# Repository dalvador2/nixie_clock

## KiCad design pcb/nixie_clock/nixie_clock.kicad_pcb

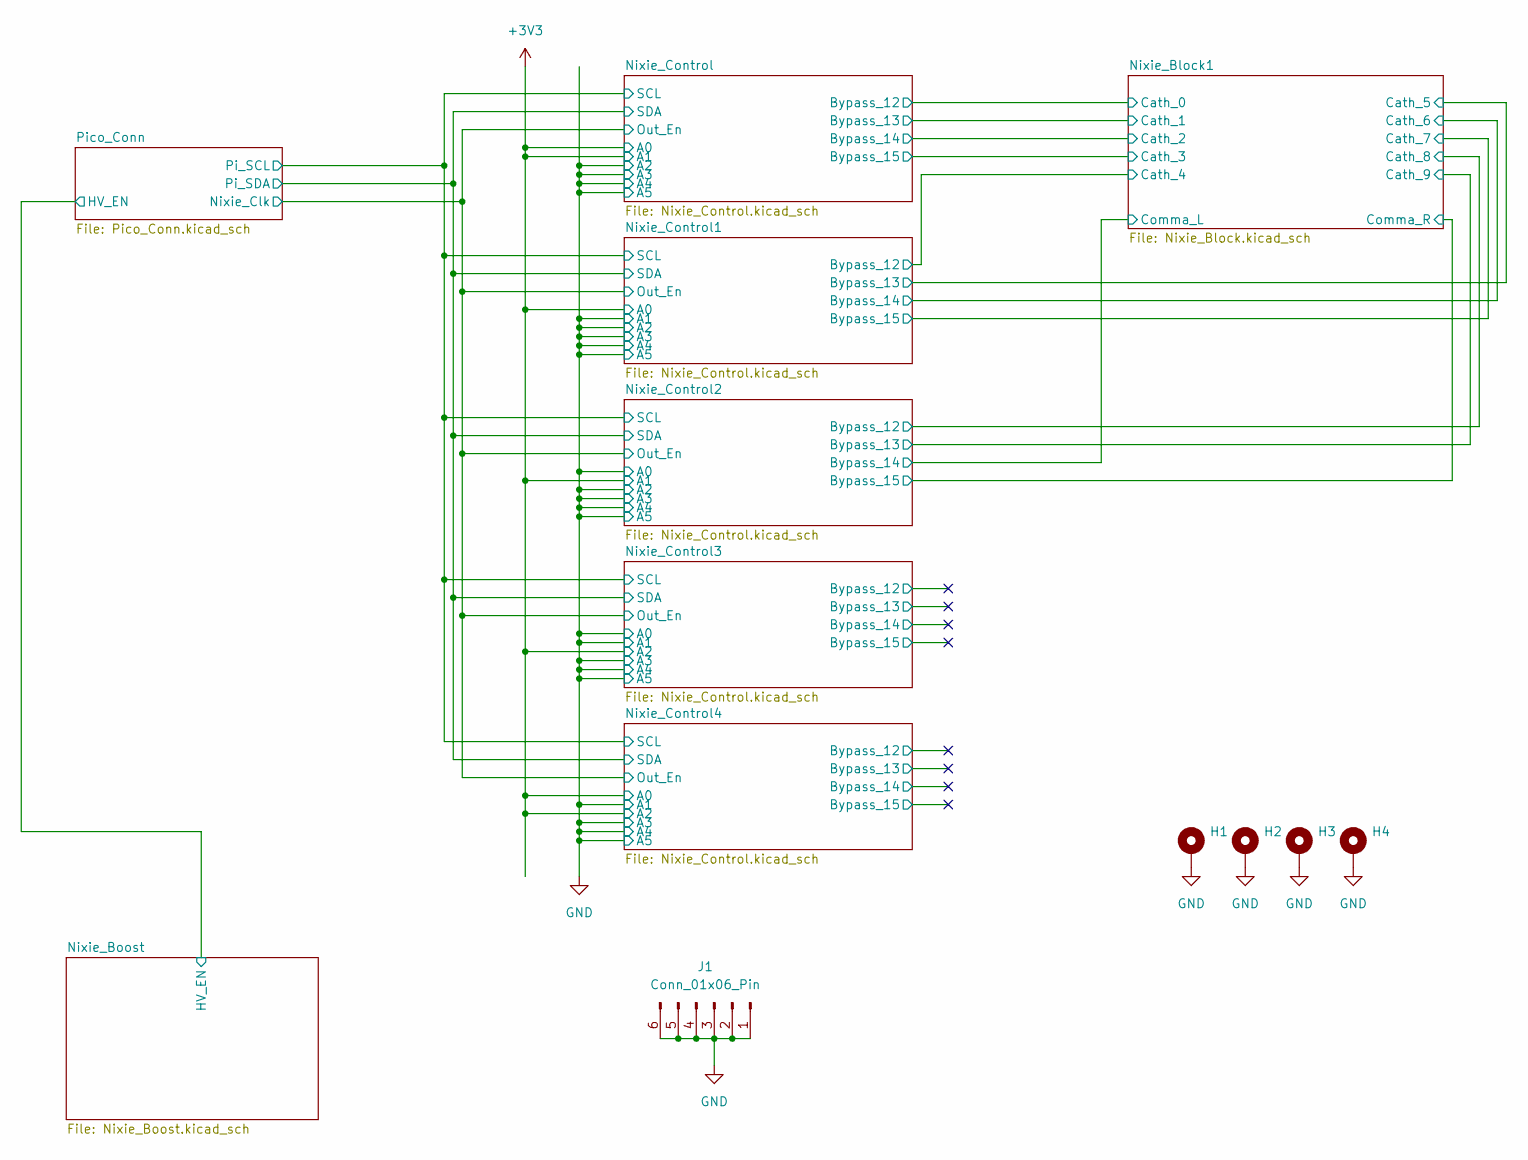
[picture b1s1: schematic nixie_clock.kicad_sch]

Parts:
H1, H2, H3, H4: MountingHole_Pad; MountingHole_2.7mm_M2.5_DIN965_Pad
J1: Conn_01x06_Pin; Molex_KK-254_AE-6410-06A_1x06_P2.54mm_Vertical

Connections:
GND: H1.1, H2.1, H3.1, H4.1, J1.1, J1.2, J1.3, J1.4, J1.5, J1.6; also elsewhere on the board

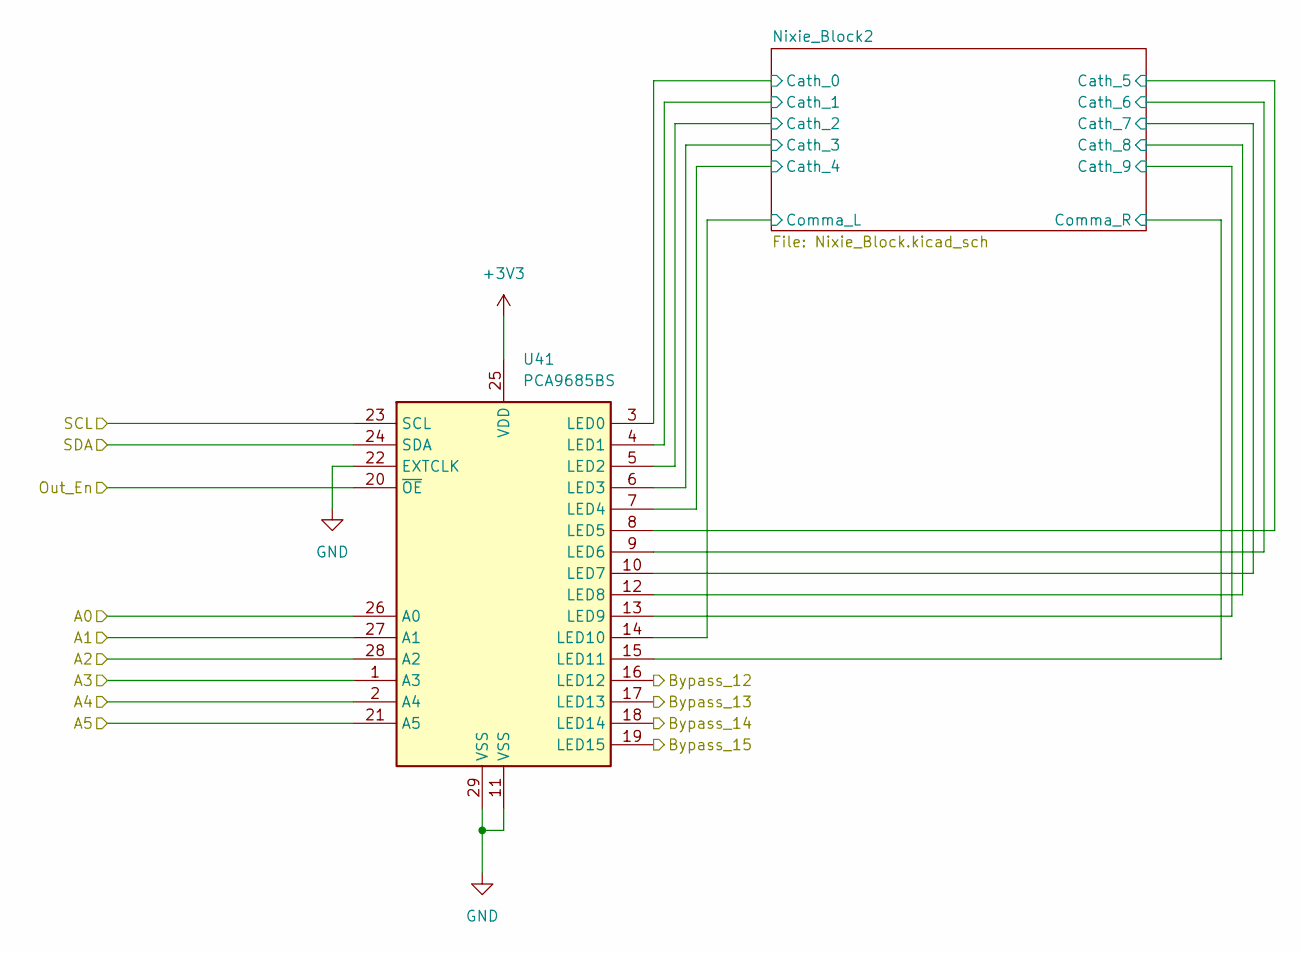
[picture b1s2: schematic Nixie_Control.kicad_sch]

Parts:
U41: PCA9685BS; QFN-28-1EP_6x6mm_P0.65mm_EP4.25x4.25mm; LCSC Part # C5191634

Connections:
+3V3: U41.25 (VDD), U41.28 (A2); also elsewhere on the board
/Nixie_Control3/Bypass_12: U41.16 (LED12)
/Nixie_Control3/Bypass_13: U41.17 (LED13)
/Nixie_Control3/Bypass_14: U41.18 (LED14)
/Nixie_Control3/Bypass_15: U41.19 (LED15)
/Nixie_Control3/Nixie_Block2/Cath_0: U41.3 (LED0); also elsewhere on the board
/Nixie_Control3/Nixie_Block2/Cath_1: U41.4 (LED1); also elsewhere on the board
/Nixie_Control3/Nixie_Block2/Cath_2: U41.5 (LED2); also elsewhere on the board
/Nixie_Control3/Nixie_Block2/Cath_3: U41.6 (LED3); also elsewhere on the board
/Nixie_Control3/Nixie_Block2/Cath_4: U41.7 (LED4); also elsewhere on the board
/Nixie_Control3/Nixie_Block2/Cath_5: U41.8 (LED5); also elsewhere on the board
/Nixie_Control3/Nixie_Block2/Cath_6: U41.9 (LED6); also elsewhere on the board
/Nixie_Control3/Nixie_Block2/Cath_7: U41.10 (LED7); also elsewhere on the board
/Nixie_Control3/Nixie_Block2/Cath_8: U41.12 (LED8); also elsewhere on the board
/Nixie_Control3/Nixie_Block2/Cath_9: U41.13 (LED9); also elsewhere on the board
/Nixie_Control3/Nixie_Block2/Comma_L: U41.14 (LED10); also elsewhere on the board
/Nixie_Control3/Nixie_Block2/Comma_R: U41.15 (LED11); also elsewhere on the board
/Nixie_Control/Out_En: U41.20 (~OE); also elsewhere on the board
/Nixie_Control/SCL: U41.23 (SCL); also elsewhere on the board
/Nixie_Control/SDA: U41.24 (SDA); also elsewhere on the board
GND: U41.1 (A3), U41.2 (A4), U41.11 (VSS), U41.21 (A5), U41.22 (EXTCLK), U41.26 (A0), U41.27 (A1), U41.29 (VSS); also elsewhere on the board

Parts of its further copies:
U13, U15, U28, U54: PCA9685BS; QFN-28-1EP_6x6mm_P0.65mm_EP4.25x4.25mm; LCSC Part # C5191634

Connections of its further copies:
+3V3: U13.25 (VDD), U13.26 (A0), U13.27 (A1), U15.25 (VDD), U15.26 (A0), U28.25 (VDD), U28.27 (A1), U54.25 (VDD), U54.26 (A0), U54.28 (A2); also elsewhere on the board
/Nixie_Block1/Cath_0: U13.16 (LED12); also elsewhere on the board
/Nixie_Block1/Cath_1: U13.17 (LED13); also elsewhere on the board
/Nixie_Block1/Cath_2: U13.18 (LED14); also elsewhere on the board
/Nixie_Block1/Cath_3: U13.19 (LED15); also elsewhere on the board
/Nixie_Block1/Cath_4: U15.16 (LED12); also elsewhere on the board
/Nixie_Block1/Cath_5: U15.17 (LED13); also elsewhere on the board
/Nixie_Block1/Cath_6: U15.18 (LED14); also elsewhere on the board
/Nixie_Block1/Cath_7: U15.19 (LED15); also elsewhere on the board
/Nixie_Block1/Cath_8: U28.16 (LED12); also elsewhere on the board
/Nixie_Block1/Cath_9: U28.17 (LED13); also elsewhere on the board
/Nixie_Block1/Comma_L: U28.18 (LED14); also elsewhere on the board
/Nixie_Block1/Comma_R: U28.19 (LED15); also elsewhere on the board
/Nixie_Control1/Nixie_Block2/Cath_0: U15.3 (LED0); also elsewhere on the board
/Nixie_Control1/Nixie_Block2/Cath_1: U15.4 (LED1); also elsewhere on the board
/Nixie_Control1/Nixie_Block2/Cath_2: U15.5 (LED2); also elsewhere on the board
/Nixie_Control1/Nixie_Block2/Cath_3: U15.6 (LED3); also elsewhere on the board
/Nixie_Control1/Nixie_Block2/Cath_4: U15.7 (LED4); also elsewhere on the board
/Nixie_Control1/Nixie_Block2/Cath_5: U15.8 (LED5); also elsewhere on the board
/Nixie_Control1/Nixie_Block2/Cath_6: U15.9 (LED6); also elsewhere on the board
/Nixie_Control1/Nixie_Block2/Cath_7: U15.10 (LED7); also elsewhere on the board
/Nixie_Control1/Nixie_Block2/Cath_8: U15.12 (LED8); also elsewhere on the board
/Nixie_Control1/Nixie_Block2/Cath_9: U15.13 (LED9); also elsewhere on the board
/Nixie_Control1/Nixie_Block2/Comma_L: U15.14 (LED10); also elsewhere on the board
/Nixie_Control1/Nixie_Block2/Comma_R: U15.15 (LED11); also elsewhere on the board
/Nixie_Control2/Nixie_Block2/Cath_0: U28.3 (LED0); also elsewhere on the board
/Nixie_Control2/Nixie_Block2/Cath_1: U28.4 (LED1); also elsewhere on the board
/Nixie_Control2/Nixie_Block2/Cath_2: U28.5 (LED2); also elsewhere on the board
/Nixie_Control2/Nixie_Block2/Cath_3: U28.6 (LED3); also elsewhere on the board
/Nixie_Control2/Nixie_Block2/Cath_4: U28.7 (LED4); also elsewhere on the board
/Nixie_Control2/Nixie_Block2/Cath_5: U28.8 (LED5); also elsewhere on the board
/Nixie_Control2/Nixie_Block2/Cath_6: U28.9 (LED6); also elsewhere on the board
/Nixie_Control2/Nixie_Block2/Cath_7: U28.10 (LED7); also elsewhere on the board
/Nixie_Control2/Nixie_Block2/Cath_8: U28.12 (LED8); also elsewhere on the board
/Nixie_Control2/Nixie_Block2/Cath_9: U28.13 (LED9); also elsewhere on the board
/Nixie_Control2/Nixie_Block2/Comma_L: U28.14 (LED10); also elsewhere on the board
/Nixie_Control2/Nixie_Block2/Comma_R: U28.15 (LED11); also elsewhere on the board
/Nixie_Control4/Bypass_12: U54.16 (LED12)
/Nixie_Control4/Bypass_13: U54.17 (LED13)
/Nixie_Control4/Bypass_14: U54.18 (LED14)
/Nixie_Control4/Bypass_15: U54.19 (LED15)
/Nixie_Control4/Nixie_Block2/Cath_0: U54.3 (LED0); also elsewhere on the board
/Nixie_Control4/Nixie_Block2/Cath_1: U54.4 (LED1); also elsewhere on the board
/Nixie_Control4/Nixie_Block2/Cath_2: U54.5 (LED2); also elsewhere on the board
/Nixie_Control4/Nixie_Block2/Cath_3: U54.6 (LED3); also elsewhere on the board
/Nixie_Control4/Nixie_Block2/Cath_4: U54.7 (LED4); also elsewhere on the board
/Nixie_Control4/Nixie_Block2/Cath_5: U54.8 (LED5); also elsewhere on the board
/Nixie_Control4/Nixie_Block2/Cath_6: U54.9 (LED6); also elsewhere on the board
/Nixie_Control4/Nixie_Block2/Cath_7: U54.10 (LED7); also elsewhere on the board
/Nixie_Control4/Nixie_Block2/Cath_8: U54.12 (LED8); also elsewhere on the board
/Nixie_Control4/Nixie_Block2/Cath_9: U54.13 (LED9); also elsewhere on the board
/Nixie_Control4/Nixie_Block2/Comma_L: U54.14 (LED10); also elsewhere on the board
/Nixie_Control4/Nixie_Block2/Comma_R: U54.15 (LED11); also elsewhere on the board
/Nixie_Control/Nixie_Block2/Cath_0: U13.3 (LED0); also elsewhere on the board
/Nixie_Control/Nixie_Block2/Cath_1: U13.4 (LED1); also elsewhere on the board
/Nixie_Control/Nixie_Block2/Cath_2: U13.5 (LED2); also elsewhere on the board
/Nixie_Control/Nixie_Block2/Cath_3: U13.6 (LED3); also elsewhere on the board
/Nixie_Control/Nixie_Block2/Cath_4: U13.7 (LED4); also elsewhere on the board
/Nixie_Control/Nixie_Block2/Cath_5: U13.8 (LED5); also elsewhere on the board
/Nixie_Control/Nixie_Block2/Cath_6: U13.9 (LED6); also elsewhere on the board
/Nixie_Control/Nixie_Block2/Cath_7: U13.10 (LED7); also elsewhere on the board
/Nixie_Control/Nixie_Block2/Cath_8: U13.12 (LED8); also elsewhere on the board
/Nixie_Control/Nixie_Block2/Cath_9: U13.13 (LED9); also elsewhere on the board
/Nixie_Control/Nixie_Block2/Comma_L: U13.14 (LED10); also elsewhere on the board
/Nixie_Control/Nixie_Block2/Comma_R: U13.15 (LED11); also elsewhere on the board
/Nixie_Control/Out_En: U13.20 (~OE), U15.20 (~OE), U28.20 (~OE), U54.20 (~OE); also elsewhere on the board
/Nixie_Control/SCL: U13.23 (SCL), U15.23 (SCL), U28.23 (SCL), U54.23 (SCL); also elsewhere on the board
/Nixie_Control/SDA: U13.24 (SDA), U15.24 (SDA), U28.24 (SDA), U54.24 (SDA); also elsewhere on the board
GND: U13.1 (A3), U13.2 (A4), U13.11 (VSS), U13.21 (A5), U13.22 (EXTCLK), U13.28 (A2), U13.29 (VSS), U15.1 (A3), U15.2 (A4), U15.11 (VSS), U15.21 (A5), U15.22 (EXTCLK), U15.27 (A1), U15.28 (A2), U15.29 (VSS), U28.1 (A3), U28.2 (A4), U28.11 (VSS), U28.21 (A5), U28.22 (EXTCLK), U28.26 (A0), U28.28 (A2), U28.29 (VSS), U54.1 (A3), U54.2 (A4), U54.11 (VSS), U54.21 (A5), U54.22 (EXTCLK), U54.27 (A1), U54.29 (VSS); also elsewhere on the board

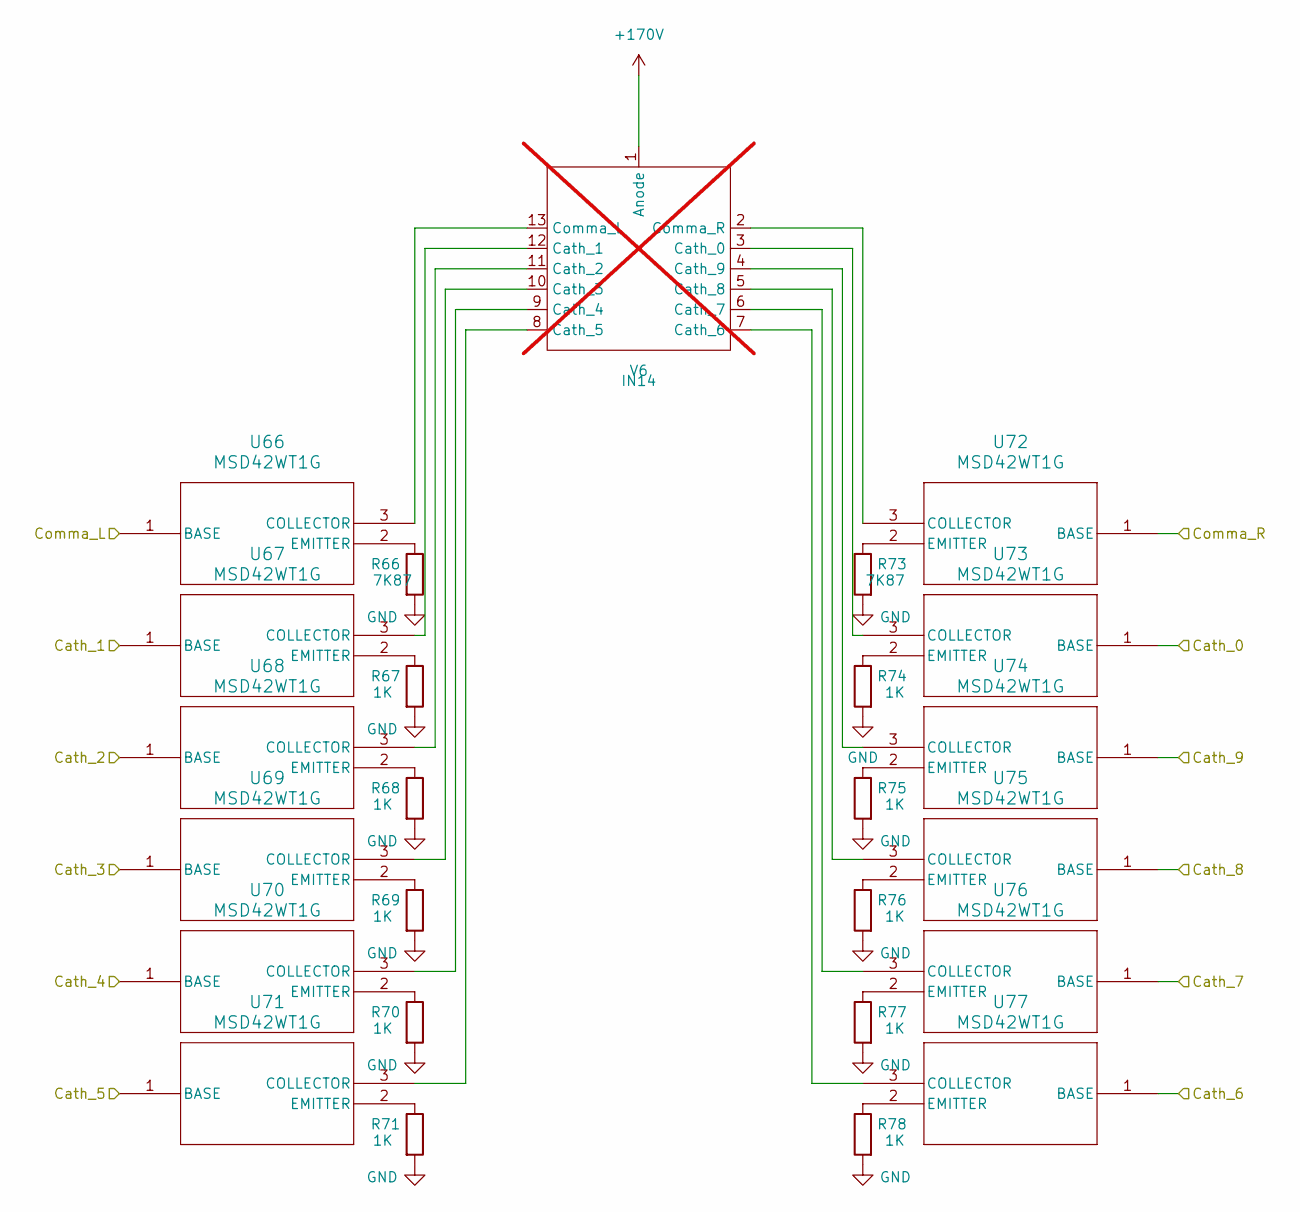
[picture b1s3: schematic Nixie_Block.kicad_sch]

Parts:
R66, R73: 7K87; R_0603_1608Metric; LCSC Part # C137680
R67, R68, R69, R70, R71, R74, R75, R76, R77, R78: 1K; R_0603_1608Metric; LCSC Part # C22548
U66, U67, U68, U69, U70, U71, U72, U73, U74, U75, U76, U77: MSD42WT1G; SOT-323-3_2P2X1P35_ONS; LCSC Part # C891781
V6: IN14; not fitted

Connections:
+170V: V6.1 (Anode); also elsewhere on the board
/Nixie_Block1/Cath_0: U67.1 (BASE); also elsewhere on the board
/Nixie_Block1/Cath_1: U73.1 (BASE); also elsewhere on the board
/Nixie_Block1/Cath_2: U74.1 (BASE); also elsewhere on the board
/Nixie_Block1/Cath_3: U75.1 (BASE); also elsewhere on the board
/Nixie_Block1/Cath_4: U76.1 (BASE); also elsewhere on the board
/Nixie_Block1/Cath_5: U77.1 (BASE); also elsewhere on the board
/Nixie_Block1/Cath_6: U71.1 (BASE); also elsewhere on the board
/Nixie_Block1/Cath_7: U70.1 (BASE); also elsewhere on the board
/Nixie_Block1/Cath_8: U69.1 (BASE); also elsewhere on the board
/Nixie_Block1/Cath_9: U68.1 (BASE); also elsewhere on the board
/Nixie_Block1/Comma_L: U72.1 (BASE); also elsewhere on the board
/Nixie_Block1/Comma_R: U66.1 (BASE); also elsewhere on the board
GND: R66.2, R67.2, R68.2, R69.2, R70.2, R71.2, R73.2, R74.2, R75.2, R76.2, R77.2, R78.2; also elsewhere on the board
unnamed: U66.3 (COLLECTOR), V6.13 (Comma_R)
unnamed: R66.1, U66.2 (EMITTER)
unnamed: U67.3 (COLLECTOR), V6.12 (Cath_0)
unnamed: R67.1, U67.2 (EMITTER)
unnamed: U68.3 (COLLECTOR), V6.11 (Cath_9)
unnamed: R68.1, U68.2 (EMITTER)
unnamed: U69.3 (COLLECTOR), V6.10 (Cath_8)
unnamed: R69.1, U69.2 (EMITTER)
unnamed: U70.3 (COLLECTOR), V6.9 (Cath_7)
unnamed: R70.1, U70.2 (EMITTER)
unnamed: U71.3 (COLLECTOR), V6.8 (Cath_6)
unnamed: R71.1, U71.2 (EMITTER)
unnamed: U72.3 (COLLECTOR), V6.2 (Comma_L)
unnamed: R73.1, U72.2 (EMITTER)
unnamed: U73.3 (COLLECTOR), V6.3 (Cath_1)
unnamed: R74.1, U73.2 (EMITTER)
unnamed: U74.3 (COLLECTOR), V6.4 (Cath_2)
unnamed: R75.1, U74.2 (EMITTER)
unnamed: U75.3 (COLLECTOR), V6.5 (Cath_3)
unnamed: R76.1, U75.2 (EMITTER)
unnamed: U76.3 (COLLECTOR), V6.6 (Cath_4)
unnamed: R77.1, U76.2 (EMITTER)
unnamed: U77.3 (COLLECTOR), V6.7 (Cath_5)
unnamed: R78.1, U77.2 (EMITTER)

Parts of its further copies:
R1, R7, R13, R19, R25, R31, R37, R43, R49, R55: 7K87; R_0603_1608Metric; LCSC Part # C137680
R2, R3, R4, R5, R6, R8, R9, R10, R11, R12, R14, R15, R16, R17, R18, R20, R21, R22, R23, R24, R26, R27, R28, R29, R30, R32, R33, R34, R35, R36, R38, R39, R40, R41, R42, R44, R45, R46, R47, R48, R50, R51, R52, R53, R54, R56, R57, R58, R59, R60: 1K; R_0603_1608Metric; LCSC Part # C22548
U1, U2, U3, U4, U5, U6, U7, U8, U9, U10, U11, U12, U16, U17, U18, U19, U20, U21, U22, U23, U24, U25, U26, U27, U29, U30, U31, U32, U33, U34, U35, U36, U37, U38, U39, U40, U42, U43, U44, U45, U46, U47, U48, U49, U50, U51, U52, U53, U55, U56, U57, U58, U59, U60, U61, U62, U63, U64, U65, U78: MSD42WT1G; SOT-323-3_2P2X1P35_ONS; LCSC Part # C891781
V1, V2, V3, V4, V5: IN14; not fitted

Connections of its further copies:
+170V: V1.1 (Anode), V2.1 (Anode), V3.1 (Anode), V4.1 (Anode), V5.1 (Anode); also elsewhere on the board
/Nixie_Control1/Nixie_Block2/Cath_0: U17.1 (BASE); also elsewhere on the board
/Nixie_Control1/Nixie_Block2/Cath_1: U23.1 (BASE); also elsewhere on the board
/Nixie_Control1/Nixie_Block2/Cath_2: U24.1 (BASE); also elsewhere on the board
/Nixie_Control1/Nixie_Block2/Cath_3: U25.1 (BASE); also elsewhere on the board
/Nixie_Control1/Nixie_Block2/Cath_4: U26.1 (BASE); also elsewhere on the board
/Nixie_Control1/Nixie_Block2/Cath_5: U27.1 (BASE); also elsewhere on the board
/Nixie_Control1/Nixie_Block2/Cath_6: U21.1 (BASE); also elsewhere on the board
/Nixie_Control1/Nixie_Block2/Cath_7: U20.1 (BASE); also elsewhere on the board
/Nixie_Control1/Nixie_Block2/Cath_8: U19.1 (BASE); also elsewhere on the board
/Nixie_Control1/Nixie_Block2/Cath_9: U18.1 (BASE); also elsewhere on the board
/Nixie_Control1/Nixie_Block2/Comma_L: U22.1 (BASE); also elsewhere on the board
/Nixie_Control1/Nixie_Block2/Comma_R: U16.1 (BASE); also elsewhere on the board
/Nixie_Control2/Nixie_Block2/Cath_0: U30.1 (BASE); also elsewhere on the board
/Nixie_Control2/Nixie_Block2/Cath_1: U36.1 (BASE); also elsewhere on the board
/Nixie_Control2/Nixie_Block2/Cath_2: U37.1 (BASE); also elsewhere on the board
/Nixie_Control2/Nixie_Block2/Cath_3: U38.1 (BASE); also elsewhere on the board
/Nixie_Control2/Nixie_Block2/Cath_4: U39.1 (BASE); also elsewhere on the board
/Nixie_Control2/Nixie_Block2/Cath_5: U40.1 (BASE); also elsewhere on the board
/Nixie_Control2/Nixie_Block2/Cath_6: U34.1 (BASE); also elsewhere on the board
/Nixie_Control2/Nixie_Block2/Cath_7: U33.1 (BASE); also elsewhere on the board
/Nixie_Control2/Nixie_Block2/Cath_8: U32.1 (BASE); also elsewhere on the board
/Nixie_Control2/Nixie_Block2/Cath_9: U31.1 (BASE); also elsewhere on the board
/Nixie_Control2/Nixie_Block2/Comma_L: U35.1 (BASE); also elsewhere on the board
/Nixie_Control2/Nixie_Block2/Comma_R: U29.1 (BASE); also elsewhere on the board
/Nixie_Control3/Nixie_Block2/Cath_0: U43.1 (BASE); also elsewhere on the board
/Nixie_Control3/Nixie_Block2/Cath_1: U49.1 (BASE); also elsewhere on the board
/Nixie_Control3/Nixie_Block2/Cath_2: U50.1 (BASE); also elsewhere on the board
/Nixie_Control3/Nixie_Block2/Cath_3: U51.1 (BASE); also elsewhere on the board
/Nixie_Control3/Nixie_Block2/Cath_4: U52.1 (BASE); also elsewhere on the board
/Nixie_Control3/Nixie_Block2/Cath_5: U53.1 (BASE); also elsewhere on the board
/Nixie_Control3/Nixie_Block2/Cath_6: U47.1 (BASE); also elsewhere on the board
/Nixie_Control3/Nixie_Block2/Cath_7: U46.1 (BASE); also elsewhere on the board
/Nixie_Control3/Nixie_Block2/Cath_8: U45.1 (BASE); also elsewhere on the board
/Nixie_Control3/Nixie_Block2/Cath_9: U44.1 (BASE); also elsewhere on the board
/Nixie_Control3/Nixie_Block2/Comma_L: U48.1 (BASE); also elsewhere on the board
/Nixie_Control3/Nixie_Block2/Comma_R: U42.1 (BASE); also elsewhere on the board
/Nixie_Control4/Nixie_Block2/Cath_0: U56.1 (BASE); also elsewhere on the board
/Nixie_Control4/Nixie_Block2/Cath_1: U62.1 (BASE); also elsewhere on the board
/Nixie_Control4/Nixie_Block2/Cath_2: U63.1 (BASE); also elsewhere on the board
/Nixie_Control4/Nixie_Block2/Cath_3: U64.1 (BASE); also elsewhere on the board
/Nixie_Control4/Nixie_Block2/Cath_4: U65.1 (BASE); also elsewhere on the board
/Nixie_Control4/Nixie_Block2/Cath_5: U78.1 (BASE); also elsewhere on the board
/Nixie_Control4/Nixie_Block2/Cath_6: U60.1 (BASE); also elsewhere on the board
/Nixie_Control4/Nixie_Block2/Cath_7: U59.1 (BASE); also elsewhere on the board
/Nixie_Control4/Nixie_Block2/Cath_8: U58.1 (BASE); also elsewhere on the board
/Nixie_Control4/Nixie_Block2/Cath_9: U57.1 (BASE); also elsewhere on the board
/Nixie_Control4/Nixie_Block2/Comma_L: U61.1 (BASE); also elsewhere on the board
/Nixie_Control4/Nixie_Block2/Comma_R: U55.1 (BASE); also elsewhere on the board
/Nixie_Control/Nixie_Block2/Cath_0: U2.1 (BASE); also elsewhere on the board
/Nixie_Control/Nixie_Block2/Cath_1: U8.1 (BASE); also elsewhere on the board
/Nixie_Control/Nixie_Block2/Cath_2: U9.1 (BASE); also elsewhere on the board
/Nixie_Control/Nixie_Block2/Cath_3: U10.1 (BASE); also elsewhere on the board
/Nixie_Control/Nixie_Block2/Cath_4: U11.1 (BASE); also elsewhere on the board
/Nixie_Control/Nixie_Block2/Cath_5: U12.1 (BASE); also elsewhere on the board
/Nixie_Control/Nixie_Block2/Cath_6: U6.1 (BASE); also elsewhere on the board
/Nixie_Control/Nixie_Block2/Cath_7: U5.1 (BASE); also elsewhere on the board
/Nixie_Control/Nixie_Block2/Cath_8: U4.1 (BASE); also elsewhere on the board
/Nixie_Control/Nixie_Block2/Cath_9: U3.1 (BASE); also elsewhere on the board
/Nixie_Control/Nixie_Block2/Comma_L: U7.1 (BASE); also elsewhere on the board
/Nixie_Control/Nixie_Block2/Comma_R: U1.1 (BASE); also elsewhere on the board
GND: R1.2, R2.2, R3.2, R4.2, R5.2, R6.2, R7.2, R8.2, R9.2, R10.2, R11.2, R12.2, R13.2, R14.2, R15.2, R16.2, R17.2, R18.2, R19.2, R20.2, R21.2, R22.2, R23.2, R24.2, R25.2, R26.2, R27.2, R28.2, R29.2, R30.2, R31.2, R32.2, R33.2, R34.2, R35.2, R36.2, R37.2, R38.2, R39.2, R40.2, R41.2, R42.2, R43.2, R44.2, R45.2, R46.2, R47.2, R48.2, R49.2, R50.2, R51.2, R52.2, R53.2, R54.2, R55.2, R56.2, R57.2, R58.2, R59.2, R60.2; also elsewhere on the board
unnamed: U1.3 (COLLECTOR), V1.13 (Comma_R)
unnamed: R1.1, U1.2 (EMITTER)
unnamed: U2.3 (COLLECTOR), V1.12 (Cath_0)
unnamed: R2.1, U2.2 (EMITTER)
unnamed: U3.3 (COLLECTOR), V1.11 (Cath_9)
unnamed: R3.1, U3.2 (EMITTER)
unnamed: U4.3 (COLLECTOR), V1.10 (Cath_8)
unnamed: R4.1, U4.2 (EMITTER)
unnamed: U5.3 (COLLECTOR), V1.9 (Cath_7)
unnamed: R5.1, U5.2 (EMITTER)
unnamed: U6.3 (COLLECTOR), V1.8 (Cath_6)
unnamed: R6.1, U6.2 (EMITTER)
unnamed: U7.3 (COLLECTOR), V1.2 (Comma_L)
unnamed: R7.1, U7.2 (EMITTER)
unnamed: U8.3 (COLLECTOR), V1.3 (Cath_1)
unnamed: R8.1, U8.2 (EMITTER)
unnamed: U9.3 (COLLECTOR), V1.4 (Cath_2)
unnamed: R9.1, U9.2 (EMITTER)
unnamed: U10.3 (COLLECTOR), V1.5 (Cath_3)
unnamed: R10.1, U10.2 (EMITTER)
unnamed: U11.3 (COLLECTOR), V1.6 (Cath_4)
unnamed: R11.1, U11.2 (EMITTER)
unnamed: U12.3 (COLLECTOR), V1.7 (Cath_5)
unnamed: R12.1, U12.2 (EMITTER)
unnamed: U16.3 (COLLECTOR), V2.13 (Comma_R)
unnamed: R13.1, U16.2 (EMITTER)
unnamed: U17.3 (COLLECTOR), V2.12 (Cath_0)
unnamed: R14.1, U17.2 (EMITTER)
unnamed: U18.3 (COLLECTOR), V2.11 (Cath_9)
unnamed: R15.1, U18.2 (EMITTER)
unnamed: U19.3 (COLLECTOR), V2.10 (Cath_8)
unnamed: R16.1, U19.2 (EMITTER)
unnamed: U20.3 (COLLECTOR), V2.9 (Cath_7)
unnamed: R17.1, U20.2 (EMITTER)
unnamed: U21.3 (COLLECTOR), V2.8 (Cath_6)
unnamed: R18.1, U21.2 (EMITTER)
unnamed: U22.3 (COLLECTOR), V2.2 (Comma_L)
unnamed: R19.1, U22.2 (EMITTER)
unnamed: U23.3 (COLLECTOR), V2.3 (Cath_1)
unnamed: R20.1, U23.2 (EMITTER)
unnamed: U24.3 (COLLECTOR), V2.4 (Cath_2)
unnamed: R21.1, U24.2 (EMITTER)
unnamed: U25.3 (COLLECTOR), V2.5 (Cath_3)
unnamed: R22.1, U25.2 (EMITTER)
unnamed: U26.3 (COLLECTOR), V2.6 (Cath_4)
unnamed: R23.1, U26.2 (EMITTER)
unnamed: U27.3 (COLLECTOR), V2.7 (Cath_5)
unnamed: R24.1, U27.2 (EMITTER)
unnamed: U29.3 (COLLECTOR), V3.13 (Comma_R)
unnamed: R25.1, U29.2 (EMITTER)
unnamed: U30.3 (COLLECTOR), V3.12 (Cath_0)
unnamed: R26.1, U30.2 (EMITTER)
unnamed: U31.3 (COLLECTOR), V3.11 (Cath_9)
unnamed: R27.1, U31.2 (EMITTER)
unnamed: U32.3 (COLLECTOR), V3.10 (Cath_8)
unnamed: R28.1, U32.2 (EMITTER)
unnamed: U33.3 (COLLECTOR), V3.9 (Cath_7)
unnamed: R29.1, U33.2 (EMITTER)
unnamed: U34.3 (COLLECTOR), V3.8 (Cath_6)
unnamed: R30.1, U34.2 (EMITTER)
unnamed: U35.3 (COLLECTOR), V3.2 (Comma_L)
unnamed: R31.1, U35.2 (EMITTER)
unnamed: U36.3 (COLLECTOR), V3.3 (Cath_1)
unnamed: R32.1, U36.2 (EMITTER)
unnamed: U37.3 (COLLECTOR), V3.4 (Cath_2)
unnamed: R33.1, U37.2 (EMITTER)
unnamed: U38.3 (COLLECTOR), V3.5 (Cath_3)
unnamed: R34.1, U38.2 (EMITTER)
unnamed: U39.3 (COLLECTOR), V3.6 (Cath_4)
unnamed: R35.1, U39.2 (EMITTER)
unnamed: U40.3 (COLLECTOR), V3.7 (Cath_5)
unnamed: R36.1, U40.2 (EMITTER)
unnamed: U42.3 (COLLECTOR), V4.13 (Comma_R)
unnamed: R37.1, U42.2 (EMITTER)
unnamed: U43.3 (COLLECTOR), V4.12 (Cath_0)
unnamed: R38.1, U43.2 (EMITTER)
unnamed: U44.3 (COLLECTOR), V4.11 (Cath_9)
unnamed: R39.1, U44.2 (EMITTER)
unnamed: U45.3 (COLLECTOR), V4.10 (Cath_8)
unnamed: R40.1, U45.2 (EMITTER)
unnamed: U46.3 (COLLECTOR), V4.9 (Cath_7)
unnamed: R41.1, U46.2 (EMITTER)
unnamed: U47.3 (COLLECTOR), V4.8 (Cath_6)
unnamed: R42.1, U47.2 (EMITTER)
unnamed: U48.3 (COLLECTOR), V4.2 (Comma_L)
unnamed: R43.1, U48.2 (EMITTER)
unnamed: U49.3 (COLLECTOR), V4.3 (Cath_1)
unnamed: R44.1, U49.2 (EMITTER)
unnamed: U50.3 (COLLECTOR), V4.4 (Cath_2)
unnamed: R45.1, U50.2 (EMITTER)
unnamed: U51.3 (COLLECTOR), V4.5 (Cath_3)
unnamed: R46.1, U51.2 (EMITTER)
unnamed: U52.3 (COLLECTOR), V4.6 (Cath_4)
unnamed: R47.1, U52.2 (EMITTER)
unnamed: U53.3 (COLLECTOR), V4.7 (Cath_5)
unnamed: R48.1, U53.2 (EMITTER)
unnamed: U55.3 (COLLECTOR), V5.13 (Comma_R)
unnamed: R49.1, U55.2 (EMITTER)
unnamed: U56.3 (COLLECTOR), V5.12 (Cath_0)
unnamed: R50.1, U56.2 (EMITTER)
unnamed: U57.3 (COLLECTOR), V5.11 (Cath_9)
unnamed: R51.1, U57.2 (EMITTER)
unnamed: U58.3 (COLLECTOR), V5.10 (Cath_8)
unnamed: R52.1, U58.2 (EMITTER)
unnamed: U59.3 (COLLECTOR), V5.9 (Cath_7)
unnamed: R53.1, U59.2 (EMITTER)
unnamed: U60.3 (COLLECTOR), V5.8 (Cath_6)
unnamed: R54.1, U60.2 (EMITTER)
unnamed: U61.3 (COLLECTOR), V5.2 (Comma_L)
unnamed: R55.1, U61.2 (EMITTER)
unnamed: U62.3 (COLLECTOR), V5.3 (Cath_1)
unnamed: R56.1, U62.2 (EMITTER)
unnamed: U63.3 (COLLECTOR), V5.4 (Cath_2)
unnamed: R57.1, U63.2 (EMITTER)
unnamed: U64.3 (COLLECTOR), V5.5 (Cath_3)
unnamed: R58.1, U64.2 (EMITTER)
unnamed: U65.3 (COLLECTOR), V5.6 (Cath_4)
unnamed: R59.1, U65.2 (EMITTER)
unnamed: U78.3 (COLLECTOR), V5.7 (Cath_5)
unnamed: R60.1, U78.2 (EMITTER)

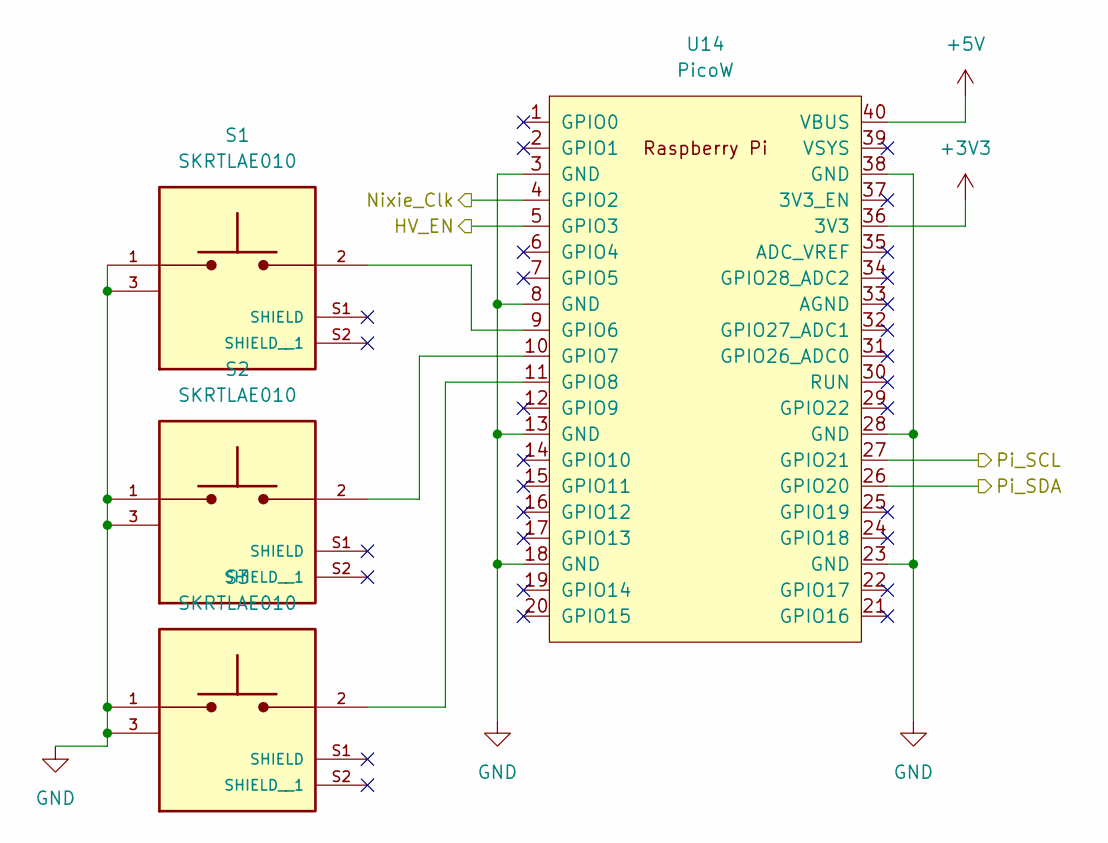
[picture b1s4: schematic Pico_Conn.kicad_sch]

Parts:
S1, S2, S3: SKRTLAE010; SW_SKRTLAE010; PARTREV --; LCSC Part # C110293
U14: PicoW; RPi_PicoW_SMD; LCSC Part # C7203003

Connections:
+3V3: U14.36 (3V3); also elsewhere on the board
+5V: U14.40 (VBUS); also elsewhere on the board
/Nixie_Boost/HV_EN: U14.5 (GPIO3); also elsewhere on the board
/Nixie_Control/Out_En: U14.4 (GPIO2); also elsewhere on the board
/Nixie_Control/SCL: U14.27 (GPIO21); also elsewhere on the board
/Nixie_Control/SDA: U14.26 (GPIO20); also elsewhere on the board
GND: S1.1, S1.3, S2.1, S2.3, S3.1, S3.3, U14.3 (GND), U14.8 (GND), U14.13 (GND), U14.18 (GND), U14.23 (GND), U14.28 (GND), U14.38 (GND); also elsewhere on the board
unnamed: S1.2, U14.9 (GPIO6)
unnamed: S2.2, U14.10 (GPIO7)
unnamed: S3.2, U14.11 (GPIO8)

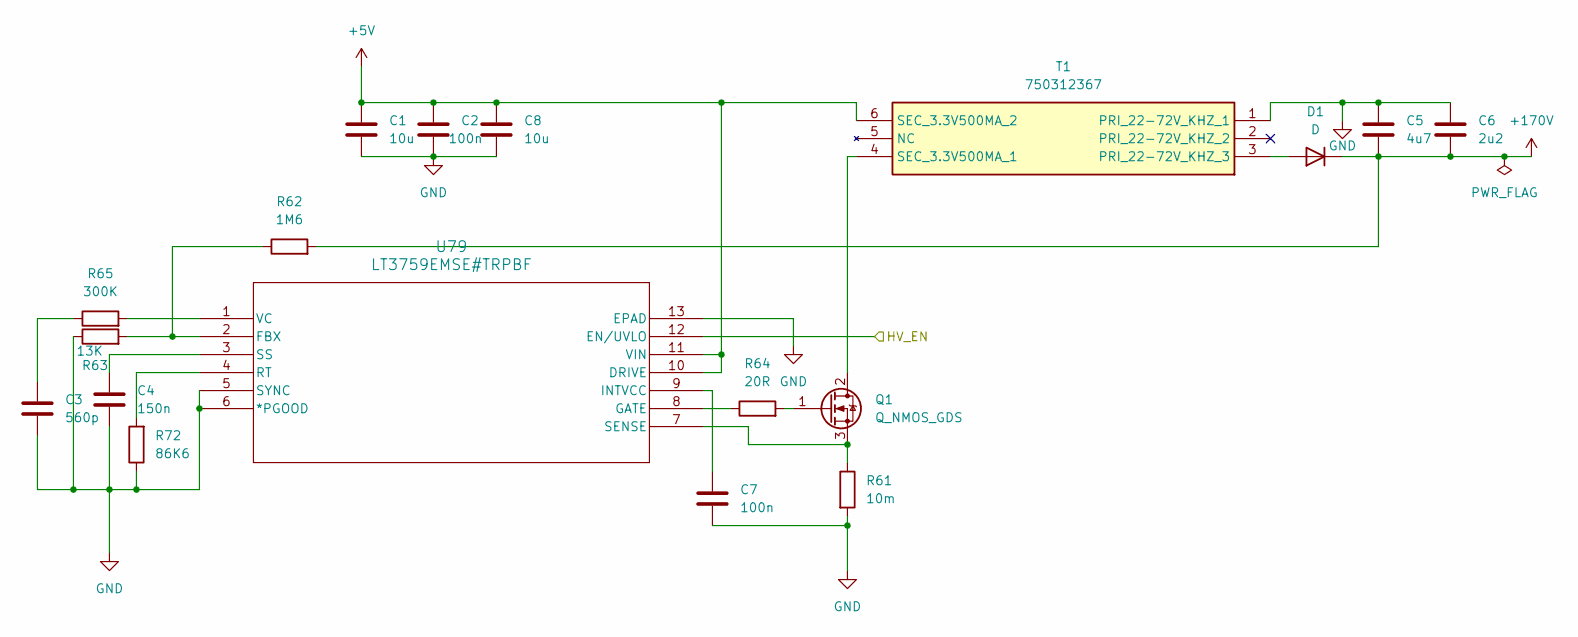
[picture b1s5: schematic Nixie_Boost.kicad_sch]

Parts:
C1, C8: 10u; C_1210_3225Metric; LCSC Part # C6477141
C2: 100n; C_0805_2012Metric; LCSC Part # C2170365
C3: 560p; C_0603_1608Metric; LCSC Part # C2171678
C4: 150n; C_0603_1608Metric; LCSC Part # C3844381
C5: 4u7; C_0603_1608Metric; LCSC Part # C3842329
C6: 2u2; C_2220_5750Metric; LCSC Part # C2168251
C7: 100n; C_1812_4532Metric; LCSC Part # C2179130
D1: D; D_SOD-123; LCSC Part # C17550678
Q1: Q_NMOS_GDS; LFPAK56; LCSC Part # C3282674
R61: 10m; R_0805_2012Metric; LCSC Part # C2977779
R62: 1M6; R_0603_1608Metric; LCSC Part # C2091296
R63: 13K; R_0603_1608Metric; LCSC Part # C402966
R64: 20R; R_0603_1608Metric; LCSC Part # C400657
R65: 300K; R_0603_1608Metric; LCSC Part # C278615
R72: 86K6; R_0603_1608Metric; LCSC Part # C2094634
T1: 750312367; Mouser Part Number 710-750312367
U79: LT3759EMSE#TRPBF; MSOP-12_MSE_LIT; LCSC Part # C580139

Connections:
+5V: C1.1, C2.1, C8.1, T1.6 (SEC_3.3V500MA_2), U79.10 (DRIVE), U79.11 (VIN); also elsewhere on the board
+170V: C5.2, C6.2, D1.1 (K), R62.2; also elsewhere on the board
/Nixie_Boost/HV_EN: U79.12 (EN/UVLO); also elsewhere on the board
GND: C1.2, C2.2, C3.2, C4.1, C5.1, C6.1, C7.2, C8.2, R61.2, R63.1, R72.1, T1.1 (PRI_22-72V_KHZ_1), U79.5 (SYNC), U79.6 (*PGOOD), U79.13 (EPAD); also elsewhere on the board
unnamed: C3.1, R65.1
unnamed: D1.2 (A), T1.3 (PRI_22-72V_KHZ_3)
unnamed: Q1.2 (D), T1.4 (SEC_3.3V500MA_1)
unnamed: Q1.1 (G), R64.2
unnamed: Q1.3 (S), R61.1, U79.7 (SENSE)
unnamed: R62.1, R63.2, U79.2 (FBX)
unnamed: R64.1, U79.8 (GATE)
unnamed: C7.1, U79.9 (INTVCC)
unnamed: R72.2, U79.4 (RT)
unnamed: C4.2, U79.3 (SS)
unnamed: R65.2, U79.1 (VC)

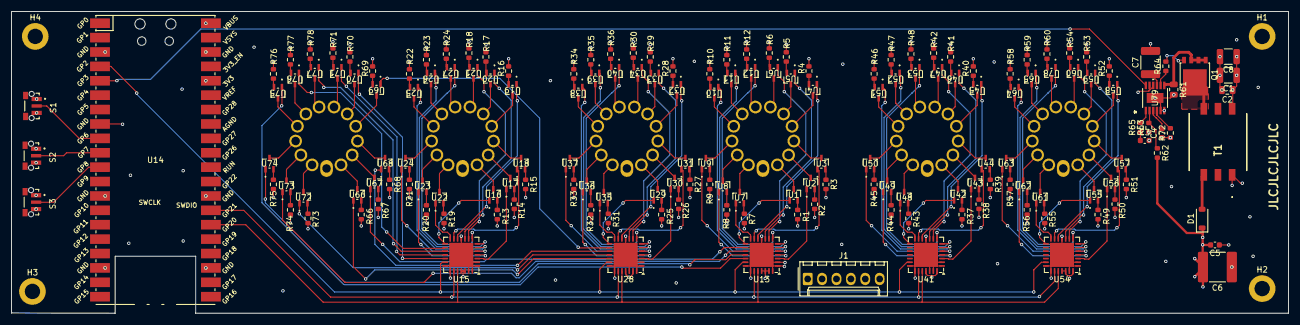
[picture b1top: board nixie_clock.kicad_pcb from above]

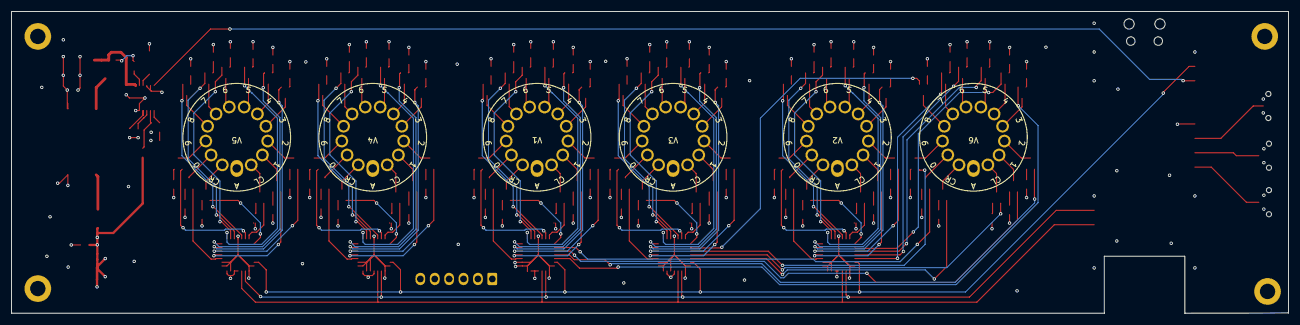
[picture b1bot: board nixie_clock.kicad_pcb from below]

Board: 6 copper layers, 225.3 x 53.2 mm, 182 parts (6 on the bottom side), 238 nets.

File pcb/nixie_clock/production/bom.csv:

Designator,Footprint,Quantity,Value,LCSC Part #
"C1, C8",1210,2,10u,C6477141
C2,0805,1,100n,C2170365
C3,0603,1,560p,C2171678
C4,0603,1,150n,C3844381
C5,0603,1,4u7,C3842329
C6,2220,1,2u2,C2168251
C7,1812,1,100n,C2179130
D1,D_SOD-123,1,D,C17550678
Q1,LFPAK56,1,Q_NMOS_GDS,C3282674
"R1, R13, R19, R25, R31, R37, R43, R49, R55, R66, R7, R73",0603,12,7K87,C137680
"R10, R11, R12, R14, R15, R16, R17, R18, R2, R20, R21, R22, R23, R24, R26, R27, R28, R29, R3, R30, R32, R33, R34, R35, R36, R38, R39, R4, R40, R41, R42, R44, R45, R46, R47, R48, R5, R50, R51, R52, R53, R54, R56, R57, R58, R59, R6, R60, R67, R68, R69, R70, R71, R74, R75, R76, R77, R78, R8, R9",0603,60,1K,C22548
R61,0805,1,10m,C2977779
R62,0603,1,1M6,C2091296
R63,0603,1,13K,C402966
R64,0603,1,20R,C400657
R65,0603,1,300K,C278615
R72,0603,1,86K6,C2094634
"S1, S2, S3",SW_SKRTLAE010,3,SKRTLAE010,C110293
T1,750312367,1,750312367,C17357180
"U1, U10, U11, U12, U16, U17, U18, U19, U2, U20, U21, U22, U23, U24, U25, U26, U27, U29, U3, U30, U31, U32, U33, U34, U35, U36, U37, U38, U39, U4, U40, U42, U43, U44, U45, U46, U47, U48, U49, U5, U50, U51, U52, U53, U55, U56, U57, U58, U59, U6, U60, U61, U62, U63, U64, U65, U66, U67, U68, U69, U7, U70, U71, U72, U73, U74, U75, U76, U77, U78, U8, U9",SOT-323-3_2P2X1P35_ONS,72,MSD42WT1G,C891781
"U13, U15, U28, U41, U54",QFN-28-1EP_6x6mm_P0.65mm_EP4.25x4.25mm,5,PCA9685BS,C5191634
U79,MSOP-12_MSE_LIT,1,LT3759EMSE#TRPBF,C580139
